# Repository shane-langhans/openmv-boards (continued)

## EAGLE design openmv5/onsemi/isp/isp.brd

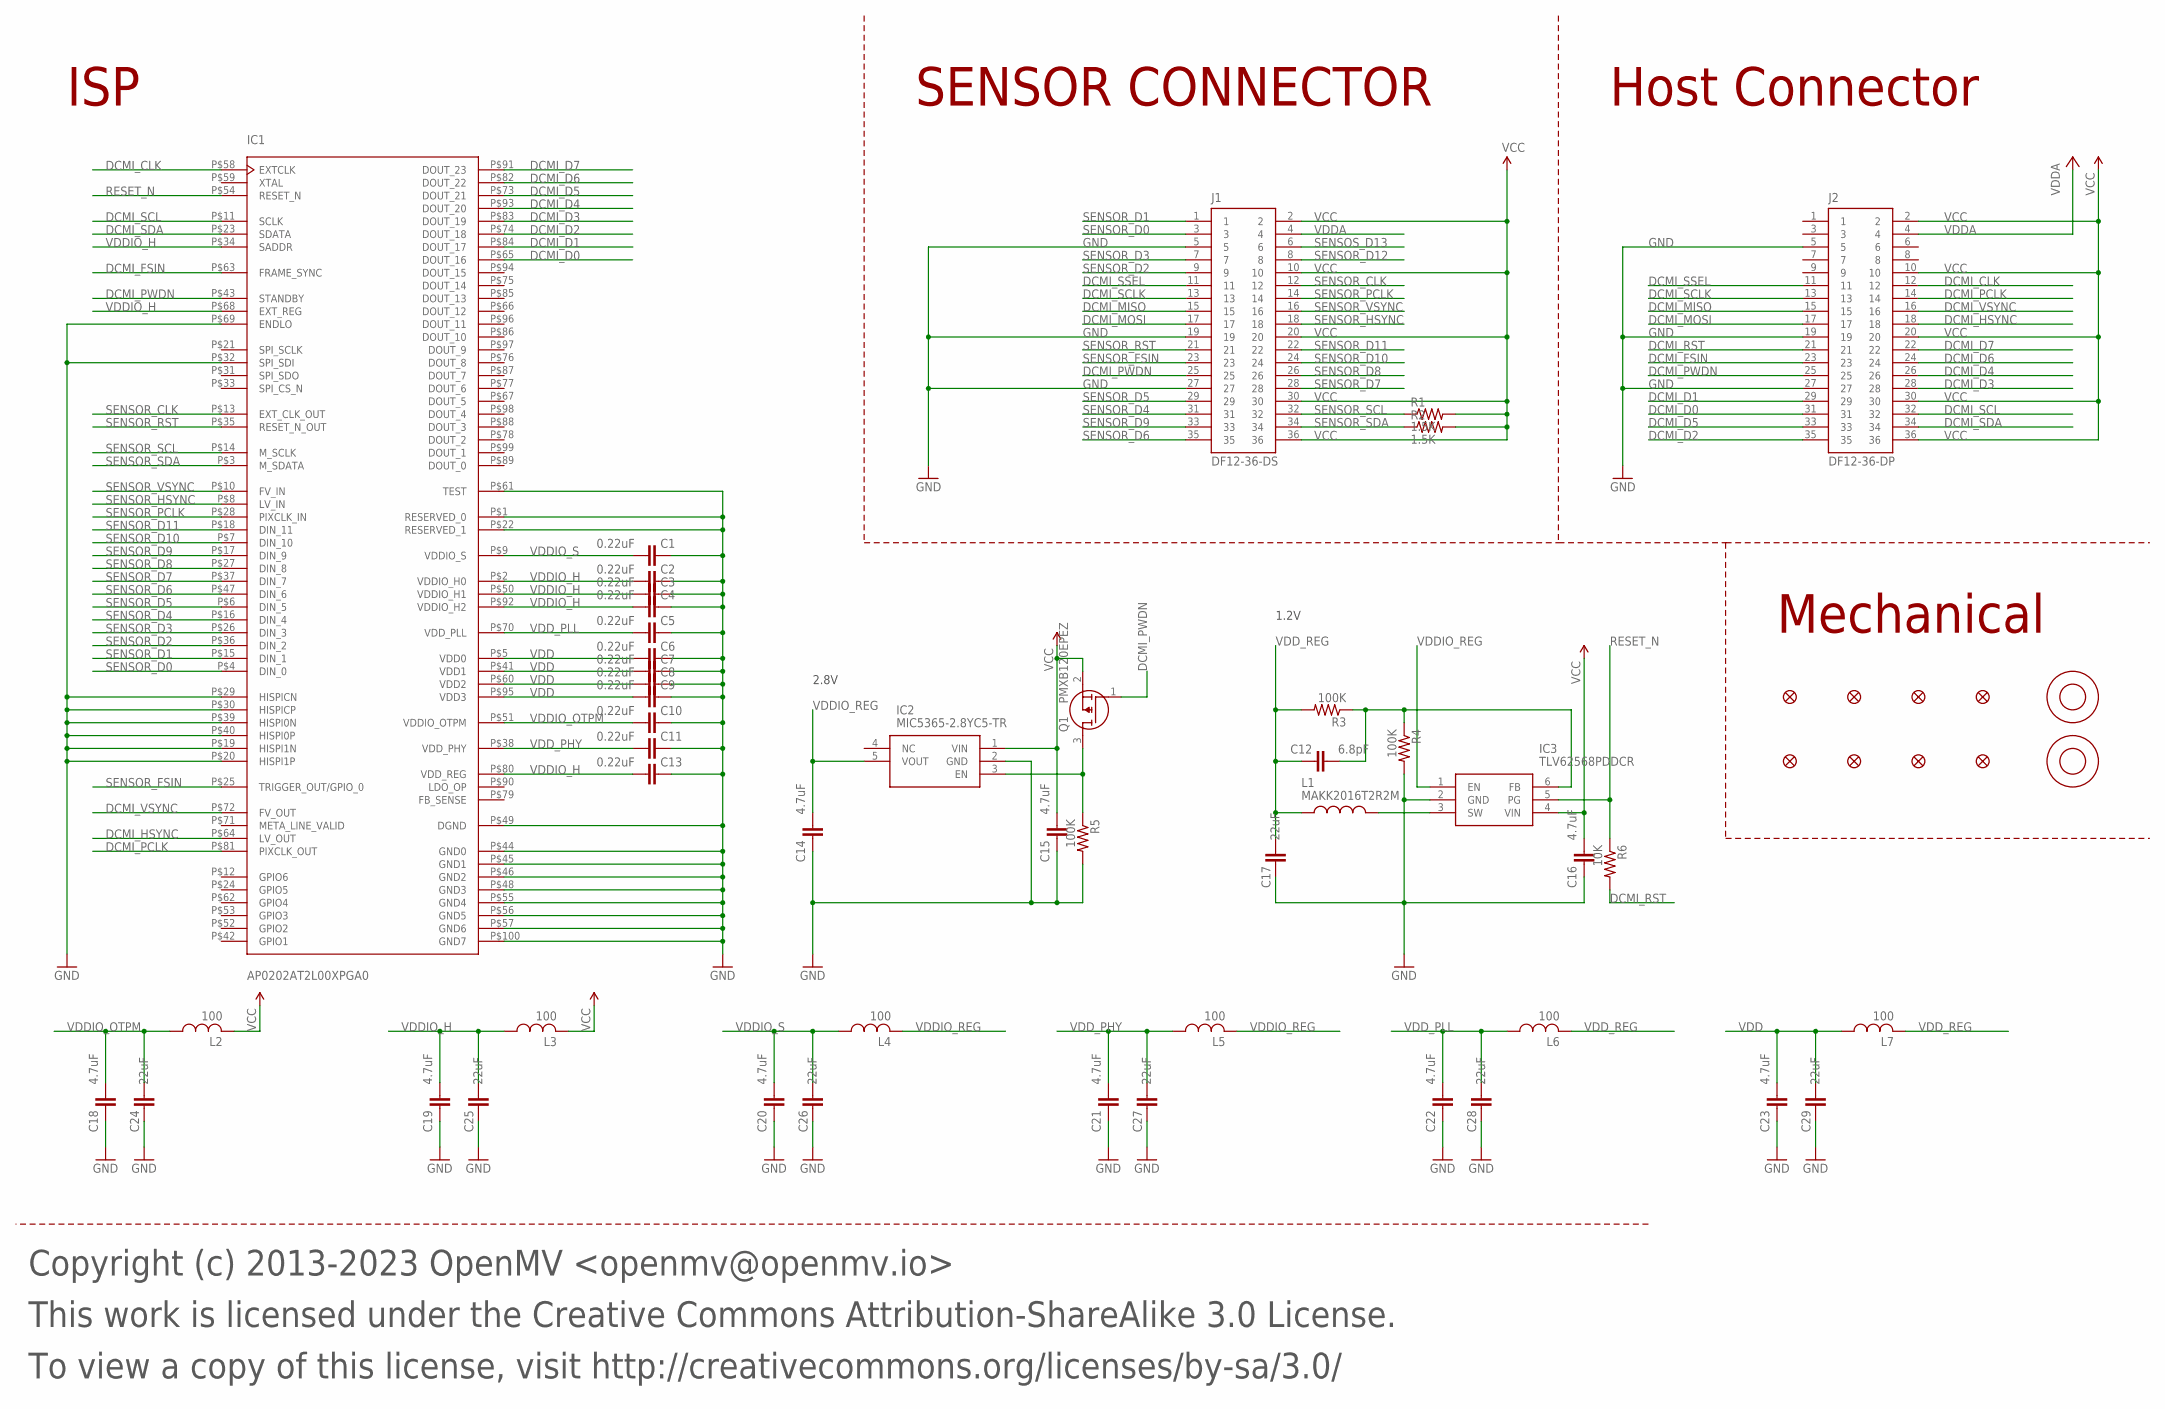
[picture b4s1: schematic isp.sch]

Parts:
C1, C2, C3, C4, C5, C6, C7, C8, C9, C10, C11, C13: 0.22uF; C0201; MPN GRM033R60J224ME15D
C12: 6.8pF; 0402; MPN GRM1555C1H6R8DA01D
C14, C15, C16, C18, C19, C20, C21, C22, C23: 4.7uF; 0402; MPN JMK105BBJ475MV-F
C17, C24, C25, C26, C27, C28, C29: 22uF; 0805; MPN CL21A226MQQNNNE
FD1, FD2, FD3, FD4, FD5, FD6, FD7, FD8: FIDUCIAL1X2; FIDUCIAL-1X2
IC1: AP0202AT2L00XPGA0; MPN AP0202AT2L00XPGA0-DR
IC2: MIC5365-2.8YC5-TR; SOT65P210X110-5N; MPN MIC5365-2.8YC5-TR
IC3: TLV62568PDDCR; SOT95P280X110-6N; MPN TLV62568PDDCR
J1: DF12-36-DS; MPN DF12NB-36DS-0.5V(51)
J2: DF12-36-DP; MPN DF12NB(3.0)-36DP-0.5V(51)
L1: MAKK2016T2R2M; INDC2016X100N; MPN MAKK2016T2R2M
L2, L3, L4, L5, L6, L7: 100; 0402; MPN MFBM1V1005-101-R
M1, M2: 9774030151R; MPN 9774030151R
Q1: PMXB120EPEZ; MPN PMXB120EPEZ
R1, R2: 1.5K; R0402; MPN RC0402FR-131K5L
R3, R4, R5: 100K; R0402; MPN AC0402FR-07100KL
R6: 10K; R0402; MPN AC0402FR-1310KL

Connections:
DCMI_CLK: IC1.P$58 (EXTCLK), J2.12
DCMI_D0: IC1.P$65 (DOUT_16), J2.31
DCMI_D1: IC1.P$84 (DOUT_17), J2.29
DCMI_D2: IC1.P$74 (DOUT_18), J2.35
DCMI_D3: IC1.P$83 (DOUT_19), J2.28
DCMI_D4: IC1.P$93 (DOUT_20), J2.26
DCMI_D5: IC1.P$73 (DOUT_21), J2.33
DCMI_D6: IC1.P$82 (DOUT_22), J2.24
DCMI_D7: IC1.P$91 (DOUT_23), J2.22
DCMI_FSIN: IC1.P$63 (FRAME_SYNC), J2.23
DCMI_HSYNC: IC1.P$64 (LV_OUT), J2.18
DCMI_MISO: J1.15, J2.15
DCMI_MOSI: J1.17, J2.17
DCMI_PCLK: IC1.P$81 (PIXCLK_OUT), J2.14
DCMI_PWDN: IC1.P$43 (STANDBY), J1.25, J2.25, Q1.1 (G)
DCMI_PWDN_INT: IC2.3 (EN), Q1.3 (D), R5.1
DCMI_RST: J2.21, R6.2
DCMI_SCL: IC1.P$11 (SCLK), J2.32
DCMI_SCLK: J1.13, J2.13
DCMI_SDA: IC1.P$23 (SDATA), J2.34
DCMI_SSEL: J1.11, J2.11
DCMI_VSYNC: IC1.P$72 (FV_OUT), J2.16
FB: C12.2, IC3.6 (FB), R3.1, R4.1
GND: C1.1, C2.1, C3.1, C4.1, C5.1, C6.1, C7.1, C8.1, C9.1, C10.1, C11.1, C13.1, C14.1, C15.1, C16.1, C17.1, C18.1, C19.1, C20.1, C21.1, C22.1, C23.1, C24.1, C25.1, C26.1, C27.1, C28.1, C29.1, IC1.P$1 (RESERVED_0), IC1.P$19 (HISPI1N), IC1.P$20 (HISPI1P), IC1.P$22 (RESERVED_1), IC1.P$29 (HISPICN), IC1.P$30 (HISPICP), IC1.P$32 (SPI_SDI), IC1.P$39 (HISPI0N), IC1.P$40 (HISPI0P), IC1.P$44 (GND0), IC1.P$45 (GND1), IC1.P$46 (GND2), IC1.P$48 (GND3), IC1.P$49 (DGND), IC1.P$55 (GND4), IC1.P$56 (GND5), IC1.P$57 (GND6), IC1.P$61 (TEST), IC1.P$69 (ENDLO), IC1.P$100 (GND7), IC2.2 (GND), IC3.2 (GND), J1.5, J1.19, J1.27, J2.5, J2.19, J2.27, R4.2, R5.2
RESET_N: IC1.P$54 (RESET_N), IC3.5 (PG), R6.1
SENSOR_CLK: IC1.P$13 (EXT_CLK_OUT), J1.12
SENSOR_D0: IC1.P$4 (DIN_0), J1.3
SENSOR_D1: IC1.P$15 (DIN_1), J1.1
SENSOR_D2: IC1.P$36 (DIN_2), J1.9
SENSOR_D3: IC1.P$26 (DIN_3), J1.7
SENSOR_D4: IC1.P$16 (DIN_4), J1.31
SENSOR_D5: IC1.P$6 (DIN_5), J1.29
SENSOR_D6: IC1.P$47 (DIN_6), J1.35
SENSOR_D7: IC1.P$37 (DIN_7), J1.28
SENSOR_D8: IC1.P$27 (DIN_8), J1.26
SENSOR_D9: IC1.P$17 (DIN_9), J1.33
SENSOR_D10: IC1.P$7 (DIN_10), J1.24
SENSOR_D11: IC1.P$18 (DIN_11), J1.22
SENSOR_D12: J1.8
SENSOR_FSIN: IC1.P$25 (TRIGGER_OUT/GPIO_0), J1.23
SENSOR_HSYNC: IC1.P$8 (LV_IN), J1.18
SENSOR_PCLK: IC1.P$28 (PIXCLK_IN), J1.14
SENSOR_RST: IC1.P$35 (RESET_N_OUT), J1.21
SENSOR_SCL: IC1.P$14 (M_SCLK), J1.32, R1.1
SENSOR_SDA: IC1.P$3 (M_SDATA), J1.34, R2.1
SENSOR_VSYNC: IC1.P$10 (FV_IN), J1.16
SENSOS_D13: J1.6
SW: IC3.3 (SW), L1.2
VCC: C15.2, C16.2, IC2.1 (VIN), IC3.4 (VIN), J1.2, J1.10, J1.20, J1.30, J1.36, J2.2, J2.10, J2.20, J2.30, J2.36, L2.2, L3.2, Q1.2 (S), R1.2, R2.2
VDD: C6.2, C7.2, C8.2, C9.2, C23.2, C29.2, IC1.P$5 (VDD0), IC1.P$41 (VDD1), IC1.P$60 (VDD2), IC1.P$95 (VDD3), L7.1
VDDA: J1.4, J2.4
VDDIO_H: C2.2, C3.2, C4.2, C13.2, C19.2, C25.2, IC1.P$2 (VDDIO_H0), IC1.P$34 (SADDR), IC1.P$50 (VDDIO_H1), IC1.P$68 (EXT_REG), IC1.P$80 (VDD_REG), IC1.P$92 (VDDIO_H2), L3.1
VDDIO_OTPM: C10.2, C18.2, C24.2, IC1.P$51 (VDDIO_OTPM), L2.1
VDDIO_REG: C14.2, IC2.5 (VOUT), IC3.1 (EN), L4.2, L5.2
VDDIO_S: C1.2, C20.2, C26.2, IC1.P$9 (VDDIO_S), L4.1
VDD_PHY: C11.2, C21.2, C27.2, IC1.P$38 (VDD_PHY), L5.1
VDD_PLL: C5.2, C22.2, C28.2, IC1.P$70 (VDD_PLL), L6.1
VDD_REG: C12.1, C17.2, L1.1, L6.2, L7.2, R3.2

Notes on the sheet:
Copyright (c) 2013-2023 OpenMV <openmv@openmv.io>
This work is licensed under the Creative Commons Attribution-ShareAlike 3.0 License.
To view a copy of this license, visit http://creativecommons.org/licenses/by-sa/3.0/
ISP
Mechanical
Host Connector
1.2V
2.8V
SENSOR CONNECTOR

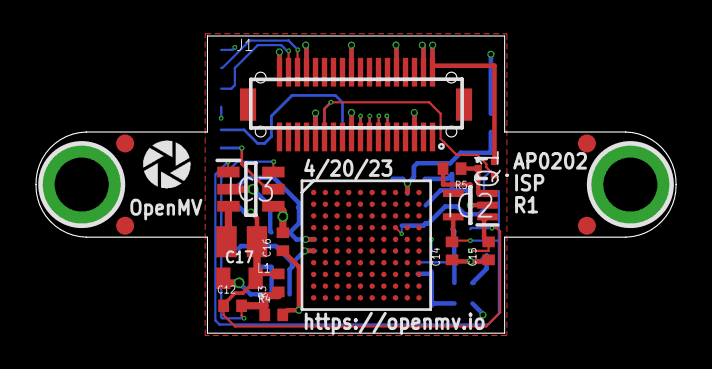
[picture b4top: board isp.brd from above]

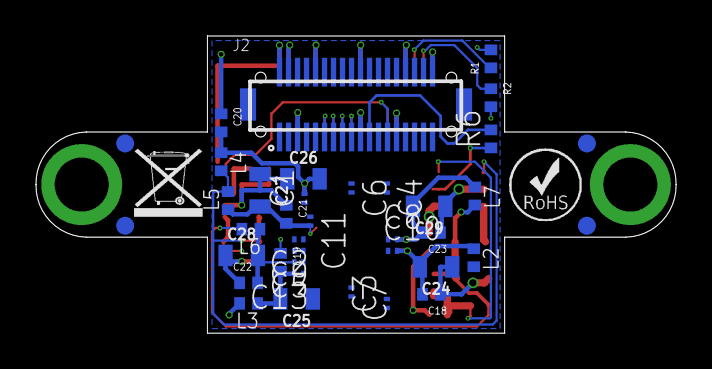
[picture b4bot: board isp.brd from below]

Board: 6 copper layers, 35.6 x 16.5 mm, 61 parts (40 on the bottom side), 56 nets.

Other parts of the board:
U$1: WEEE
U$2: ROHS
U$9: OPENMV-LOGO

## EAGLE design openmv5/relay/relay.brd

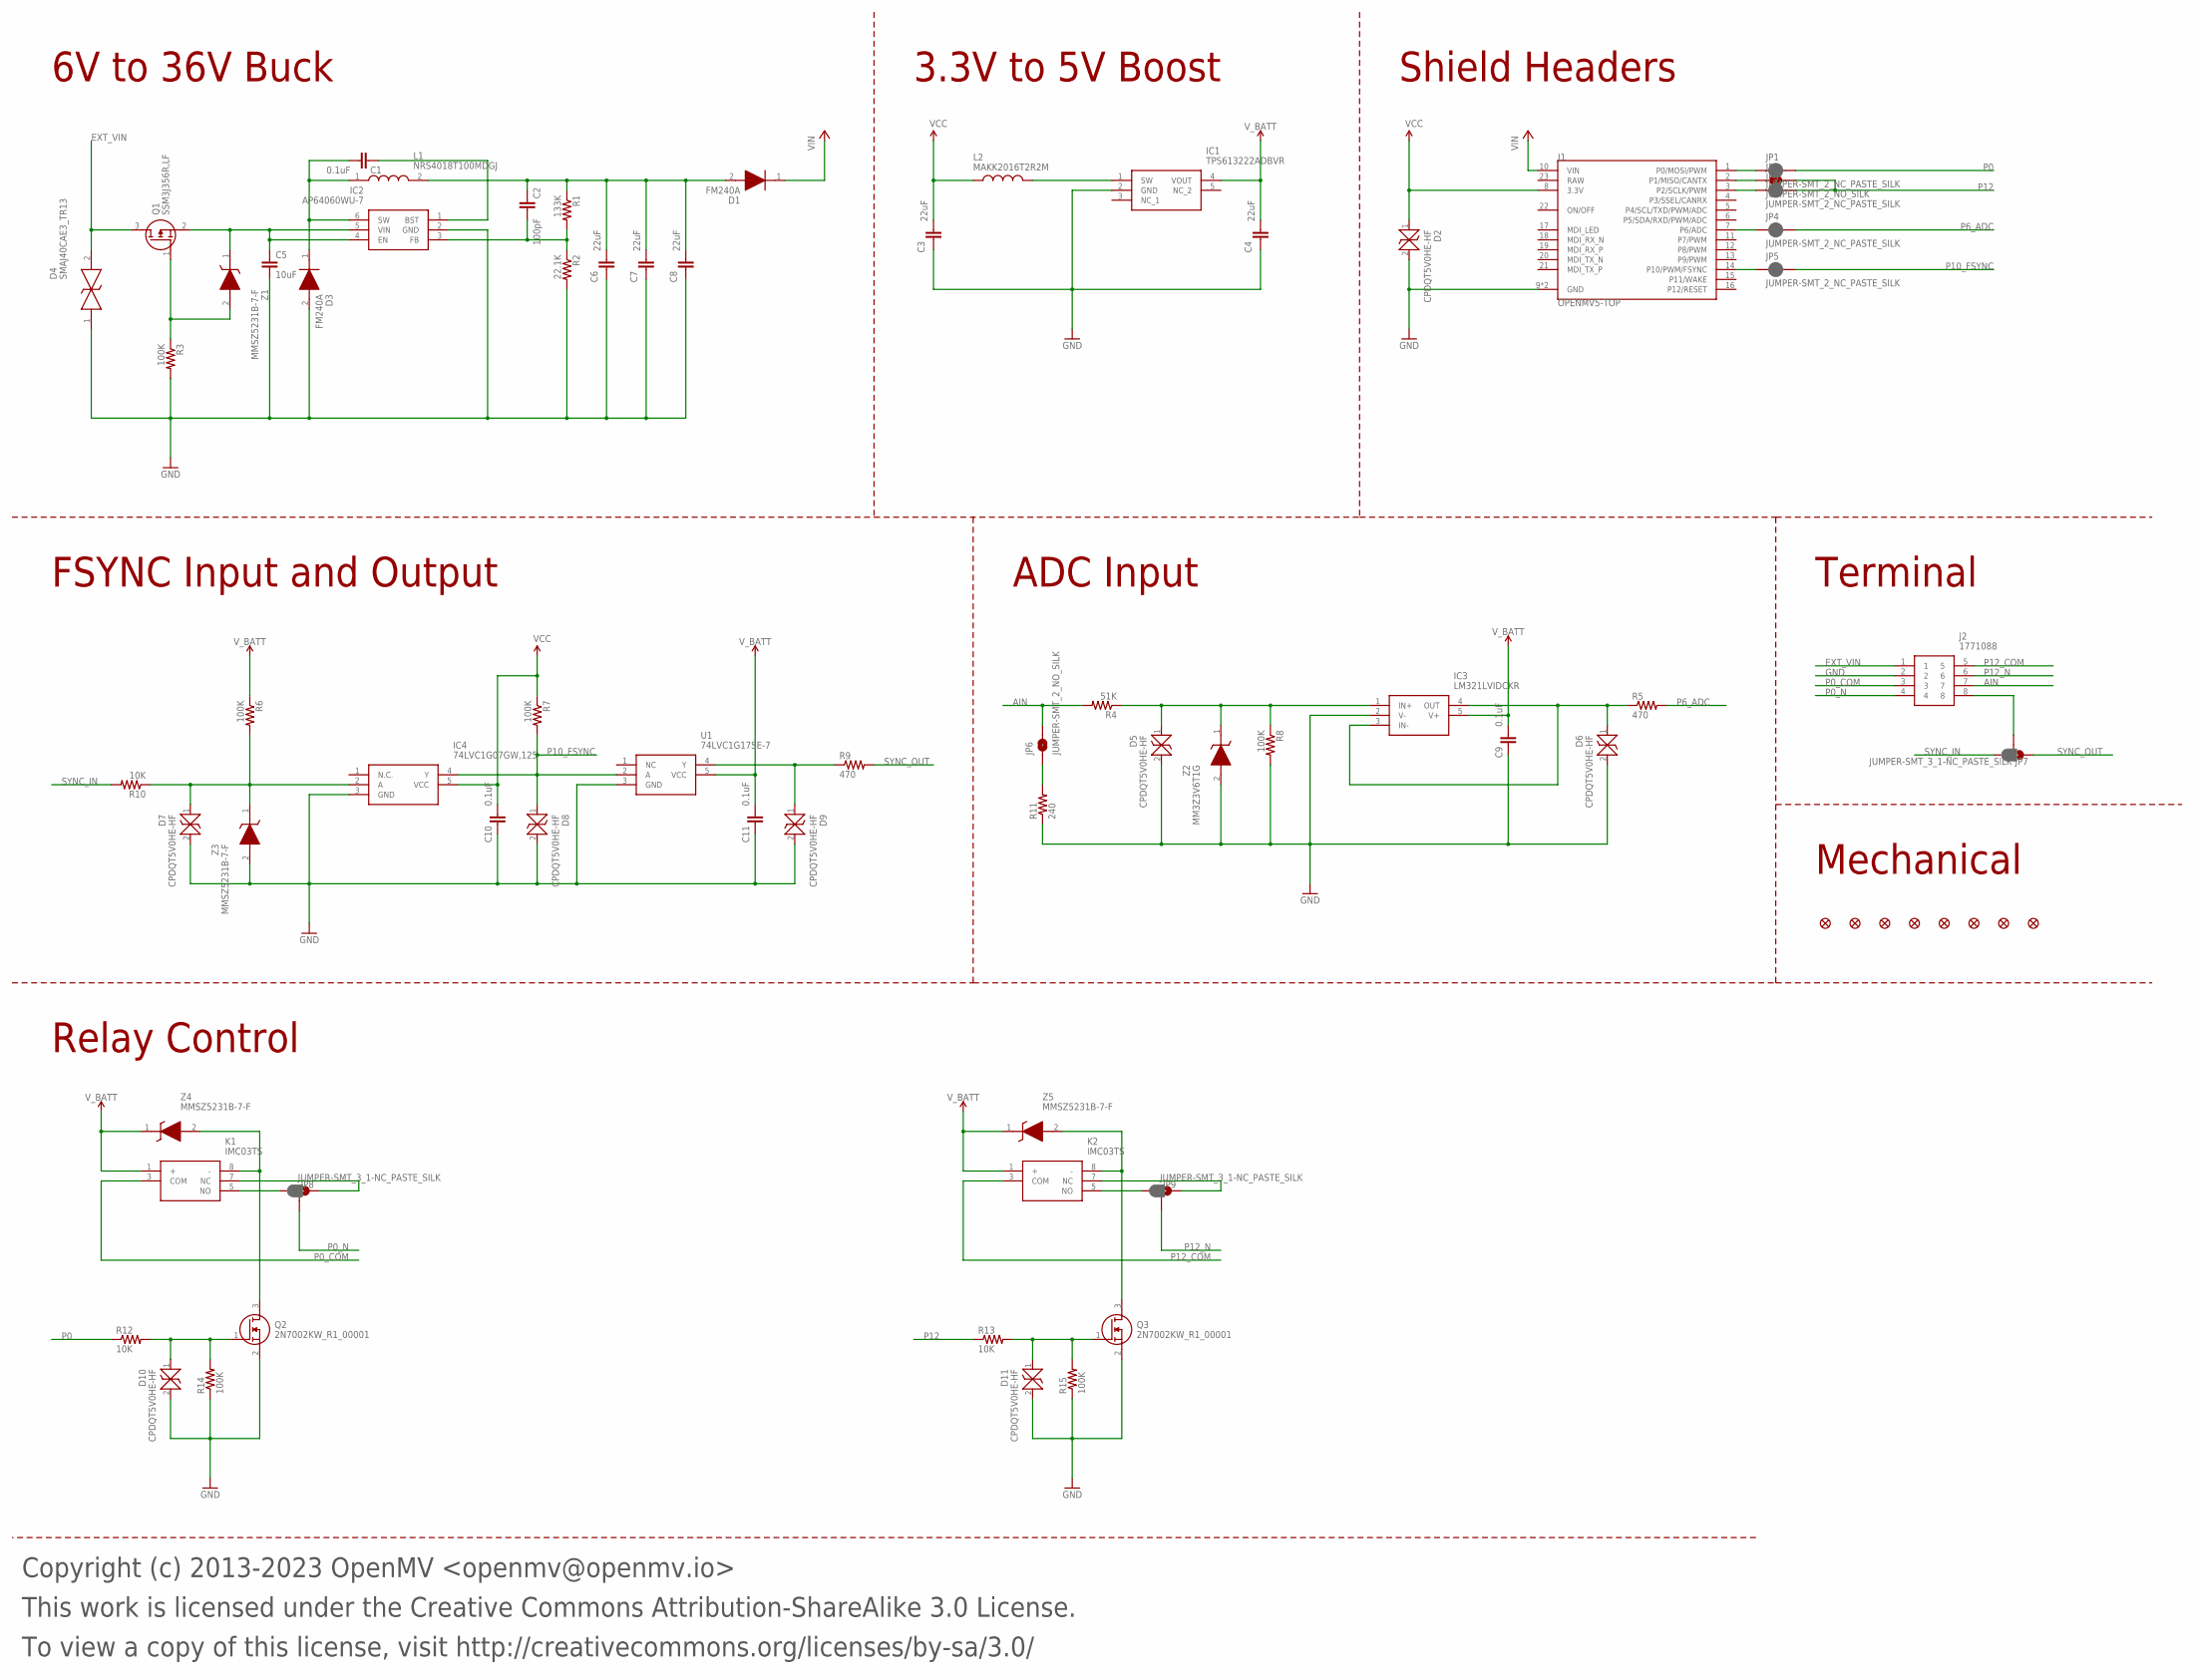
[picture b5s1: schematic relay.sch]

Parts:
C1, C9, C10, C11: 0.1uF; 0402-CAP; MPN GRM155R71H104KE14D
C2: 100pF; 0402-CAP; MPN CC0402JRNPO9BN101
C3, C4, C6, C7, C8: 22uF; 0805; MPN CL21A226MQQNNNE
C5: 10uF; C0805; MPN GRM21BR61H106KE43K
D1, D3: FM240A; DIOM5025X231N; MPN FM240A
D2, D5, D6, D7, D8, D9, D10, D11: CPDQT5V0HE-HF; CPDQT5V0HEHF; MPN CPDQT5V0HE-HF
D4: SMAJ40CAE3_TR13; SMAJ40CAE3TR13; MPN SMAJ40CAe3/TR13
FD1, FD2, FD3, FD4, FD5, FD6, FD7, FD8: FIDUCIAL1X2; FIDUCIAL-1X2
IC1: TPS613222ADBVR; SOT95P280X145-5N; MPN TPS613222ADBVR
IC2: AP64060WU-7; SOT95P280X100-6N; MPN AP64060WU-7
IC3: LM321LVIDCKR; SOT65P210X110-5N; MPN LM321LVIDCKR
IC4: 74LVC1G07GW,125; SOT65P212X110-5N; MPN 74LVC1G07GW,125
J1: OPENMV5-TOP
J2: 1771088; MPN 1771088
JP1, JP3, JP4, JP5: JUMPER-SMT_2_NC_PASTE_SILK; SMT-JUMPER_2_NC_PASTE_SILK
JP2, JP6: JUMPER-SMT_2_NO_SILK; SMT-JUMPER_2_NO_SILK
JP7, JP8, JP9: JUMPER-SMT_3_1-NC_PASTE_SILK; SMT-JUMPER_3_1-NC_PASTE_SILK
K1, K2: IMC03TS; MPN IMC03CTS
L1: NRS4018T100MDGJ; MPN NRS4018T100MDGJ
L2: MAKK2016T2R2M; INDC2016X100N; MPN MAKK2016T2R2M
Q1: SSM3J356R,LF; SOTFL95P240X88-3N; MPN SSM3J356R,LF
Q2, Q3: 2N7002KW_R1_00001; SOT65P210X110-3N; MPN 2N7002KW_R1_00001
R1: 133K; 0402-RES; MPN RC0402FR-07133KL
R2: 22.1K; 0402-RES; MPN CR0402-FX-2212GLF
R3, R6, R7, R8, R14, R15: 100K; 0402-RES; MPN AC0402FR-07100KL
R4: 51K; 0402-RES; MPN RC0402JR-0751KL
R5, R9: 470; R0603; MPN CR0603-FX-4700ELF
R10, R12, R13: 10K; 0402-RES; MPN AC0402FR-1310KL
R11: 240; R0603; MPN RK73B1JTTD241J
U1: 74LVC1G17SE-7; SOT65P210X110-5N; MPN 74LVC1G17SE-7
Z1, Z3, Z4, Z5: MMSZ5231B-7-F; SOD3716X145N; MPN MMSZ5231B-7-F
Z2: MM3Z3V6T1G; SOD2512X110N; MPN MM3Z3V6T1G

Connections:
AIN: J2.7, JP6.2, R4.2
AIN_INT: D5.1, IC3.1 (IN+), R4.1, R8.1, Z2.1 (K)
AIN_OUT: D6.1, IC3.3 (IN-), IC3.4 (OUT), R5.1
AIN_S: JP6.1, R11.2
EXT_VIN: D4.2, J2.1, Q1.3 (D)
EXT_VIN_BST: C1.1, IC2.1 (BST)
EXT_VIN_FB: C2.2, IC2.3 (FB), R1.2, R2.1
EXT_VIN_G: Q1.1 (G), R3.1, Z1.2 (A)
EXT_VIN_INT: C5.1, IC2.4 (EN), IC2.5 (VIN), Q1.2 (S), Z1.1 (K)
EXT_VIN_OUT: C2.1, C6.2, C7.2, C8.2, D1.2 (A), L1.2, R1.1
EXT_VIN_SW: C1.2, D3.1 (K), IC2.6 (SW), L1.1
GND: C3.1, C4.1, C5.2, C6.1, C7.1, C8.1, C9.1, C10.1, C11.1, D2.2, D3.2 (A), D4.1, D5.2, D6.2, D7.2, D8.2, D9.2, D10.2, D11.2, IC1.2 (GND), IC2.2 (GND), IC3.2 (V-), IC4.3 (GND), J1.9 (GND), J1.24 (GND), J2.2, Q2.2 (S), Q3.2 (S), R2.2, R3.2, R8.2, R11.1, R14.1, R15.1, U1.3 (GND), Z2.2 (A), Z3.2 (A)
P0: JP1.2, R12.1
P0_COM: J2.3, K1.3 (COM)
P0_CONTROL: D10.1, Q2.1 (G), R12.2, R14.2
P0_INT: J1.1 (P0/MOSI/PWM), JP1.1
P0_N: J2.4, JP8.2
P0_NC: JP8.1, K1.7 (NC)
P0_NO: JP8.3, K1.5 (NO)
P0_RELAY: K1.8 (-), Q2.3 (D), Z4.2 (A)
P1_INT: J1.2 (P1/MISO/CANTX), JP2.1
P2_INT: J1.3 (P2/SCLK/PWM), JP3.1
P6_ADC: JP4.2, R5.2
P6_ADC_INT: J1.7 (P6/ADC), JP4.1
P10_FSYNC: D8.1, IC4.4 (Y), JP5.2, R7.2, U1.2 (A)
P10_FSYNC_INT: J1.14 (P10/PWM/FSYNC), JP5.1
P12: JP2.2, JP3.2, R13.1
P12_COM: J2.5, K2.3 (COM)
P12_CONTROL: D11.1, Q3.1 (G), R13.2, R15.2
P12_N: J2.6, JP9.2
P12_NC: JP9.1, K2.7 (NC)
P12_NO: JP9.3, K2.5 (NO)
P12_RELAY: K2.8 (-), Q3.3 (D), Z5.2 (A)
SW: IC1.1 (SW), L2.2
SYNC: J2.8, JP7.2
SYNC_IN: JP7.3, R10.2
SYNC_IN_INT: D7.1, IC4.2 (A), R6.2, R10.1, Z3.1 (K)
SYNC_OUT: JP7.1, R9.2
SYNC_OUT_INT: D9.1, R9.1, U1.4 (Y)
VCC: C3.2, C10.2, D2.1, IC4.5 (VCC), J1.8 (3.3V), L2.1, R7.1
VIN: D1.1 (K), J1.10 (VIN)
V_BATT: C4.2, C9.2, C11.2, IC1.4 (VOUT), IC3.5 (V+), K1.1 (+), K2.1 (+), R6.1, U1.5 (VCC), Z4.1 (K), Z5.1 (K)

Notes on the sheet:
Copyright (c) 2013-2023 OpenMV <openmv@openmv.io>
This work is licensed under the Creative Commons Attribution-ShareAlike 3.0 License.
To view a copy of this license, visit http://creativecommons.org/licenses/by-sa/3.0/
FSYNC Input and Output
Mechanical
Shield Headers
6V to 36V Buck
3.3V to 5V Boost
Relay Control
Terminal
ADC Input

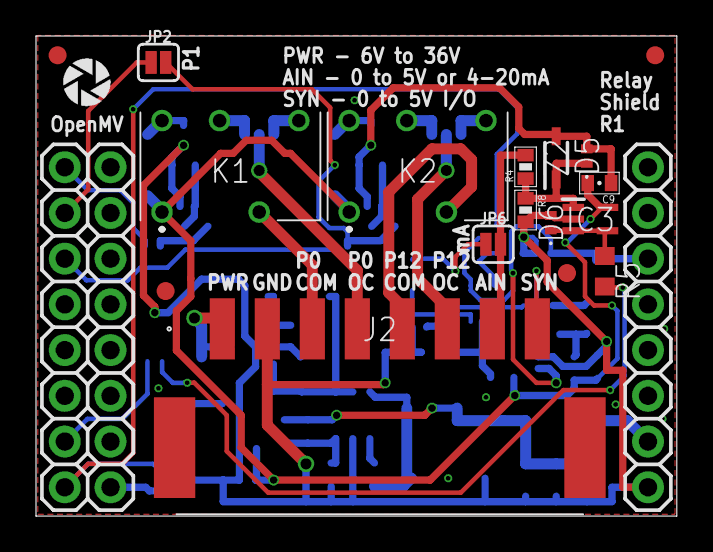
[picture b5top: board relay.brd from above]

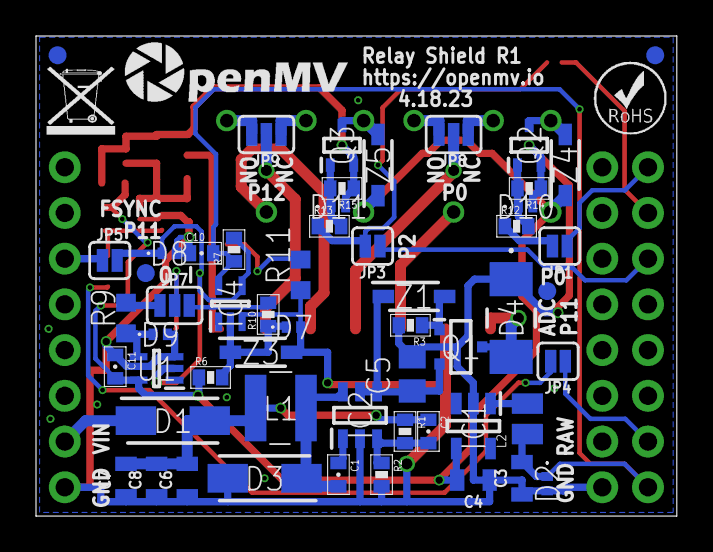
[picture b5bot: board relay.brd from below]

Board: 2 copper layers, 35.6 x 26.7 mm, 77 parts (58 on the bottom side), 42 nets.

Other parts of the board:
U$1: WEEE
U$2: ROHS
U$3: OMV-LOGO
U$9: OPENMV-LOGO

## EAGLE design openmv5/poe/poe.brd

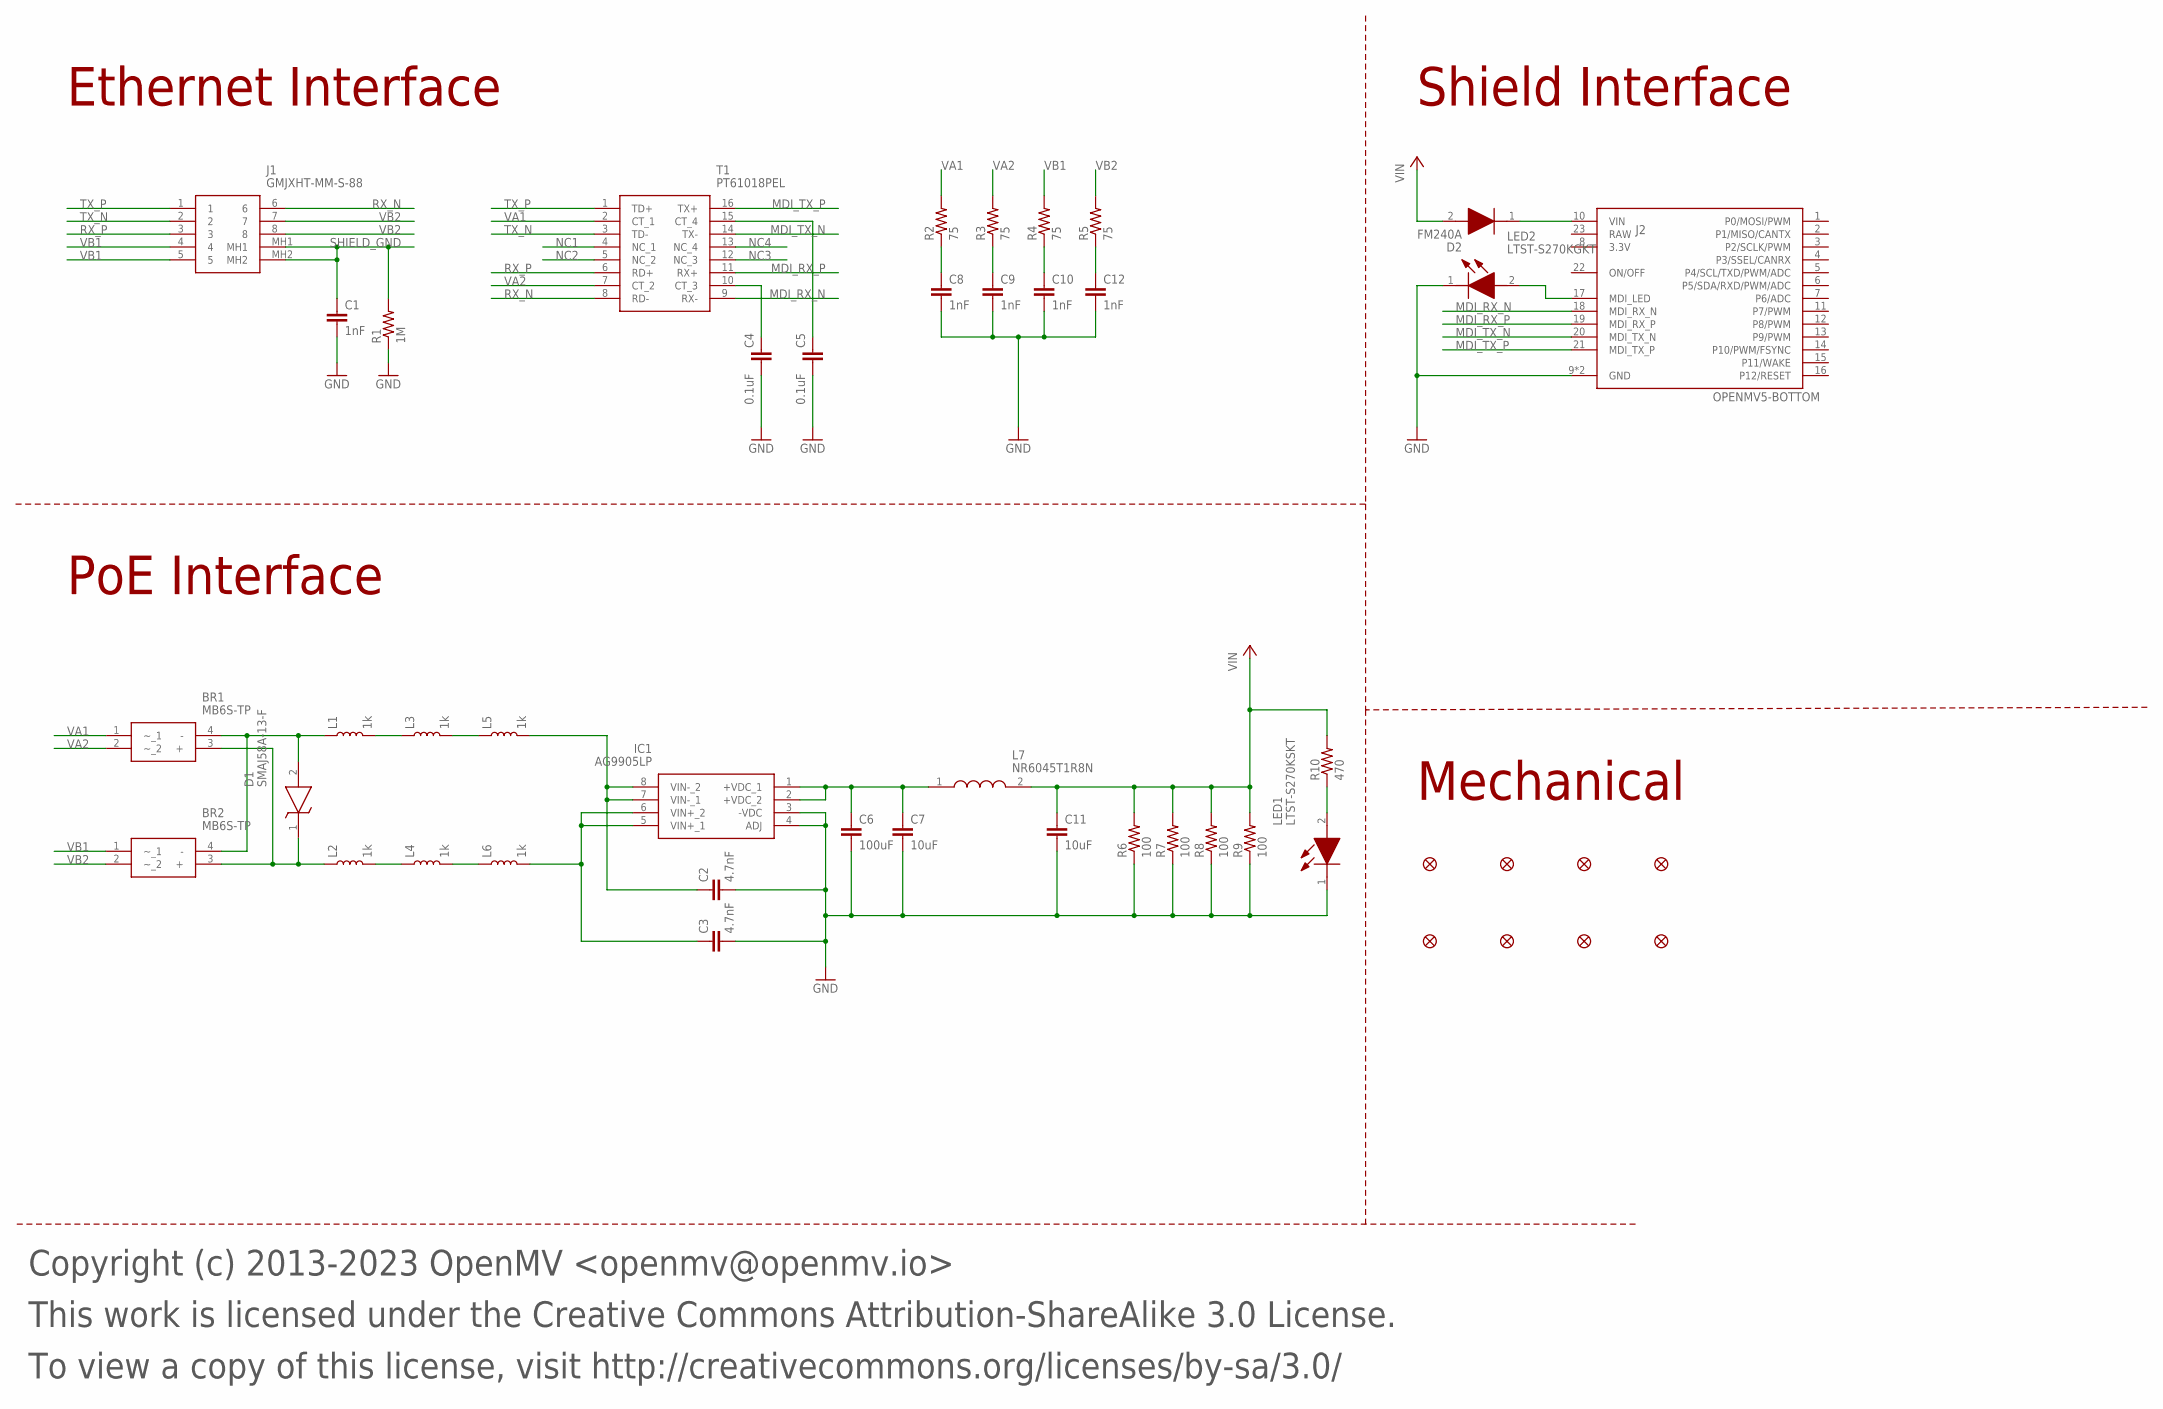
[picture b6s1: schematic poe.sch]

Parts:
BR1, BR2: MB6S-TP; SOP254P665X270-4N; MPN MB6S-TP
C1, C8, C9, C10, C12: 1nF; C1206; MPN 1206B102K252CT
C2, C3: 4.7nF; C1812; MPN 202S43W472KV4E
C4, C5: 0.1uF; C0201; MPN CL03A104KQ3NNNC
C6: 100uF; C1206; MPN CL31A107MQHNNWE
C7, C11: 10uF; C0402; MPN GRM155R60J106ME05D
D1: SMAJ58A-13-F; DIOM5226X230N; MPN SMAJ58A/TR13
D2: FM240A; DIOM5025X231N; MPN FM240A
FD1, FD2, FD3, FD4, FD5, FD6, FD7, FD8: FIDUCIAL1X2; FIDUCIAL-1X2
IC1: AG9905LP; MPN Ag9905LP
J1: GMJXHT-MM-S-88; GMJXHTMMS88; MPN GMJXHT-MM-S-88
J2: OPENMV5-BOTTOM
L1, L2, L3, L4, L5, L6: 1k; 0402; MPN BBPY00100505102Y00
L7: NR6045T1R8N; MPN NR6045T1R8N
LED1: LTST-S270KSKT; LTSTS270K; MPN LTST-S270KSKT
LED2: LTST-S270KGKT; LTSTS270K; MPN LTST-S270KGKT
R1: 1M; R1206; MPN RMCF1206FT1M00
R2, R3, R4, R5: 75; R0402; MPN 0402WGF750JTCE
R6, R7, R8, R9: 100; R2512; MPN RC2512JK-07100RL
R10: 470; R0603; MPN CR0603-FX-4700ELF
T1: PT61018PEL; SOIC127P930X565-16N; MPN PT61018PEL

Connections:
GND: C1.2, C2.2, C3.2, C4.2, C5.2, C6.2, C7.2, C8.2, C9.2, C10.2, C11.2, C12.2, IC1.3 (-VDC), IC1.4 (ADJ), J2.9 (GND), J2.24 (GND), LED1.1 (K), LED2.1 (K), R1.1, R6.1, R7.1, R8.1, R9.1
MDI_LED: J2.17 (MDI_LED), LED2.2 (A)
MDI_RX_CT: C4.1, T1.10 (CT_3)
MDI_RX_N: J2.18 (MDI_RX_N), T1.9 (RX-)
MDI_RX_P: J2.19 (MDI_RX_P), T1.11 (RX+)
MDI_TX_CT: C5.1, T1.15 (CT_4)
MDI_TX_N: J2.20 (MDI_TX_N), T1.14 (TX-)
MDI_TX_P: J2.21 (MDI_TX_P), T1.16 (TX+)
NC1: T1.4 (NC_1)
NC2: T1.5 (NC_2)
NC3: T1.12 (NC_3)
NC4: T1.13 (NC_4)
POE_VIN_INT_N: C2.1, IC1.7 (VIN-_1), IC1.8 (VIN-_2), L5.2
POE_VIN_INT_P: C3.1, IC1.5 (VIN+_1), IC1.6 (VIN+_2), L6.2
POE_VIN_N: BR1.4 (-), BR2.4 (-), D1.2 (A), L1.1
POE_VIN_N0: L1.2, L3.1
POE_VIN_N1: L3.2, L5.1
POE_VIN_P: BR1.3 (+), BR2.3 (+), D1.1 (K), L2.1
POE_VIN_P0: L2.2, L4.1
POE_VIN_P1: L4.2, L6.1
RX_N: J1.6, T1.8 (RD-)
RX_P: J1.3, T1.6 (RD+)
SHIELD_GND: C1.1, J1.MH1, J1.MH2, R1.2
TX_N: J1.2, T1.3 (TD-)
TX_P: J1.1, T1.1 (TD+)
VA1: BR1.1 (~_1), R2.2, T1.2 (CT_1)
VA1_ISO: C8.1, R2.1
VA2: BR1.2 (~_2), R3.2, T1.7 (CT_2)
VA2_ISO: C9.1, R3.1
VB1: BR2.1 (~_1), J1.4, J1.5, R4.2
VB1_ISO: C10.1, R4.1
VB2: BR2.2 (~_2), J1.7, J1.8, R5.2
VB2_ISO: C12.1, R5.1
VDC: C6.1, C7.1, IC1.1 (+VDC_1), IC1.2 (+VDC_2), L7.1
VIN: C11.1, D2.2 (A), L7.2, R6.2, R7.2, R8.2, R9.2, R10.2
VIN_INT: D2.1 (K), J2.10 (VIN)
VIN_LED: LED1.2 (A), R10.1

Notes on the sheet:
Copyright (c) 2013-2023 OpenMV <openmv@openmv.io>
This work is licensed under the Creative Commons Attribution-ShareAlike 3.0 License.
To view a copy of this license, visit http://creativecommons.org/licenses/by-sa/3.0/
Ethernet Interface
PoE Interface
Shield Interface
Mechanical

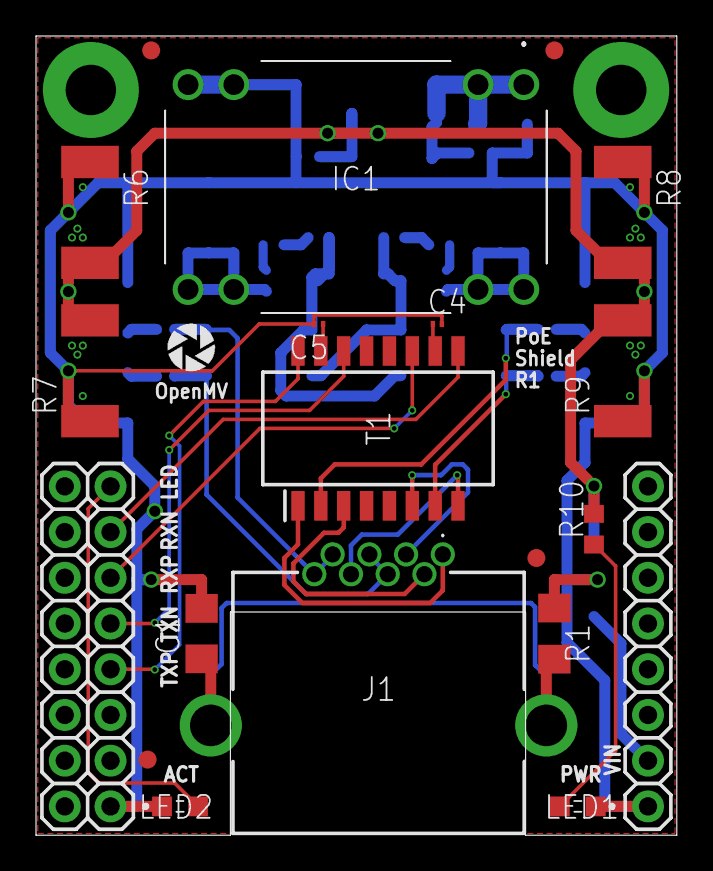
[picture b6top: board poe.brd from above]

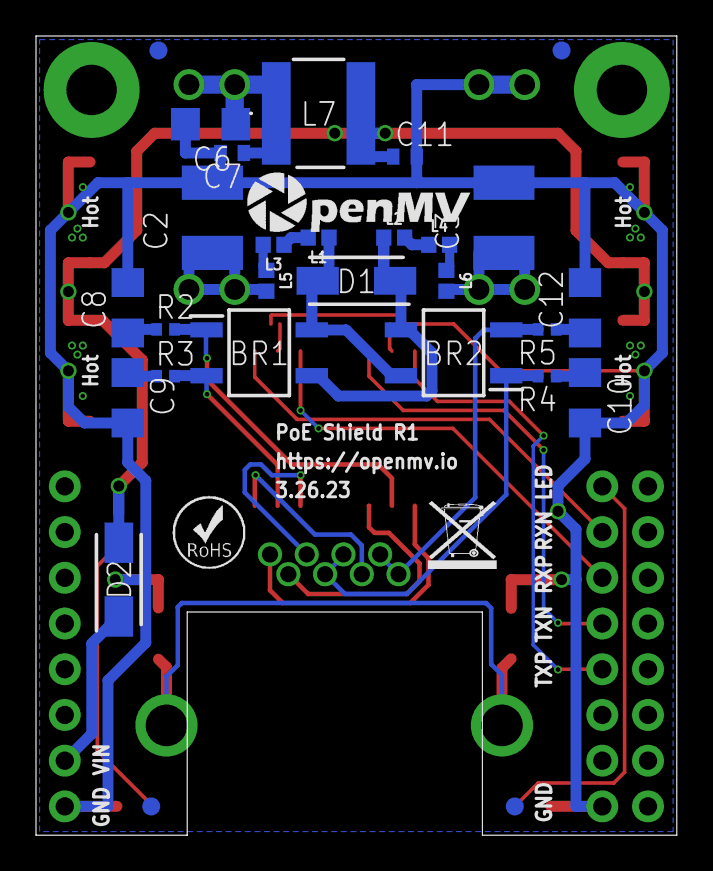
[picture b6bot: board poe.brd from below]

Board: 2 copper layers, 35.6 x 44.4 mm, 51 parts (31 on the bottom side), 33 nets.

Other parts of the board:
U$1: WEEE
U$2: ROHS
U$3: OMV-LOGO
U$9: OPENMV-LOGO

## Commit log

2023-03-24 port to altium
2023-03-26 clean up and route sdram and flash
2023-03-31 almost done
2023-03-31 routing complete
2023-04-01 updated silk, logos, etc
2023-04-01 updates and fixes
2023-04-10 generated files
2023-04-14 added PoE Shield
2023-04-15 updated p/n
2023-04-19 pir and rs232 can
2023-04-19 3d files
2023-04-20 more boards
2023-04-20 not saved
2023-04-22 3d for relay, rs485, driver
2023-04-25 fix 0402 footprints and regen photos
2023-05-01 camera modules init
2023-05-01 camera modules 2
2023-05-06 added fhd-hdr
2023-05-06 added hd-gs
2023-05-18 more camera modules completed
2023-05-28 add rt10-r2
2023-05-28 wrapped up rev 2
2023-06-01 address kwab comments
2023-06-02 address kwabs last few comments
2023-06-03 rename project and address comments
2023-06-06 ibrahim's comments
2023-06-12 finalize sensor boards
2023-06-18 added mounting support pours
2023-10-31 added ae3
2023-11-06 11-5 pm
2023-11-22 placement almost done
2023-11-26 routing started
2023-12-02 you're a dookie butt
2023-12-12 more routing
2023-12-12 almost done routing
2023-12-12 preliminary done
2023-12-14 polishing routing
2024-04-25 ae3 changes
2024-04-25 some breakouts and stm32n
2024-05-06 placement
2024-08-24 ae3 r3 n6 and pga736
2024-10-11 added updated mini ae3 r3 board
